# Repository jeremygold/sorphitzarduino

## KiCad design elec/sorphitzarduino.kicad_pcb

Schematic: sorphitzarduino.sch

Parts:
C1: 10uF; C_Radial_D5_L11_P2
C2: 4.7nF; C_Disc_D6_P5
D1: LED; LED-5MM
J1: 9V_BATT; Pin_Header_Straight_1x02
J2: SWITCH; Pin_Header_Straight_1x02
J3: AUDIO_JACK; Pin_Header_Straight_1x03
J4: Mounting Hole; MountingHole_3.2mm_M3
R1: 3.9k; Resistor_Horizontal_RM10mm
R2, R3: 1M; Resistor_Horizontal_RM10mm
R4: 290; Resistor_Horizontal_RM10mm
RV1, RV2, RV3, RV4: 10k; Bourne PTA6043
U1: ARDUINO_MICRO_SHIELD

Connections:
+5V: RV1.3, RV2.3, RV3.3, RV4.3, U1.5V (+5V), U1.AREF
GND: C1.2, C2.2, J1.2, J3.1, R4.2, RV1.1, RV2.1, RV3.1, RV4.1, U1.GND
unnamed: C1.1, J2.1, U1.VI (VIN)
unnamed: C2.1, J3.2, J3.3, R1.2, R2.2, R3.2
unnamed: D1.1 (K), R4.1
unnamed: D1.2 (A), U1.11 (11(PWM))
unnamed: J1.1, J2.2
unnamed: R1.1, U1.9 (9(PWM)/A9)
unnamed: R2.1, R3.1, U1.10 (10(PWM)/A10)
unnamed: RV1.2, U1.A0
unnamed: RV2.2, U1.A1
unnamed: RV3.2, U1.A2
unnamed: RV4.2, U1.A3

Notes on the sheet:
POWER_LED

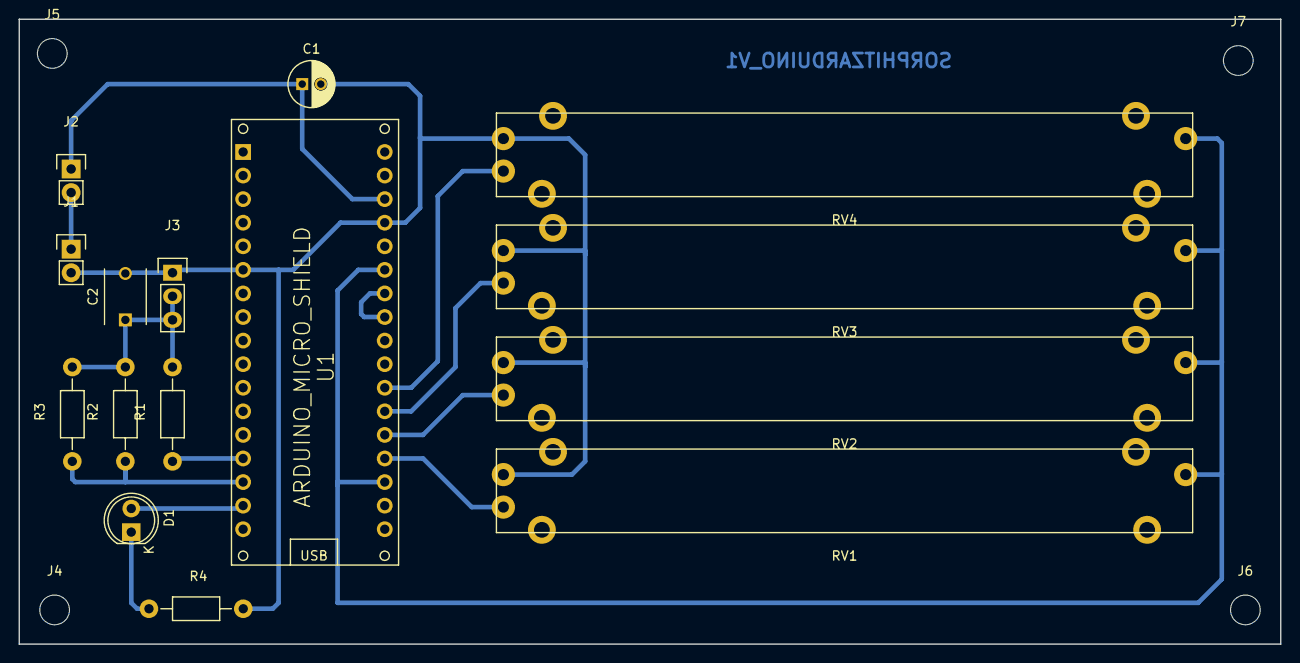
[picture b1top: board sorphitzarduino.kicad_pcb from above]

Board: 2 copper layers, 135.9 x 67.3 mm, 19 parts (0 on the bottom side), 13 nets.

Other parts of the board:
J5, J6, J7: Mounting Hole; MountingHole_3.2mm_M3

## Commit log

2018-11-19 Initial code
2018-11-19 Updating to Promethean chord with randomizer
2018-11-21 Better naming for input pins
2018-11-21 Initial attempt at frequency slider - Needs work to play nicely with randomizer
2018-11-25 Adding mozzi_config.h for customiation
2018-11-25 Initial creation of schematic and PCB layout
2018-11-25 Ignoring autosave files
2018-11-25 Saving updated pcb file
2018-11-25 Updating SVG output to be only board
2018-11-25 Save and exit
2018-12-02 Upating to HIFI output circuit, and adding sontrol of LED
2018-12-03 Initial attempts at exporting png files for cutting
2018-12-05 Generating better PNG files for milling
2018-12-09 Adding dxf for outlines
2018-12-10 Mech V1
2018-12-10 Updating to mech V2
2018-12-11 More mech updates
2018-12-11 Updating control panel
2018-12-17 Adding waveform pin
2018-12-17 Dual tone control
2018-12-17 Adding LED control
